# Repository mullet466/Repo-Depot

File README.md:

# Repo-Depot
Aaron's Repo Depot

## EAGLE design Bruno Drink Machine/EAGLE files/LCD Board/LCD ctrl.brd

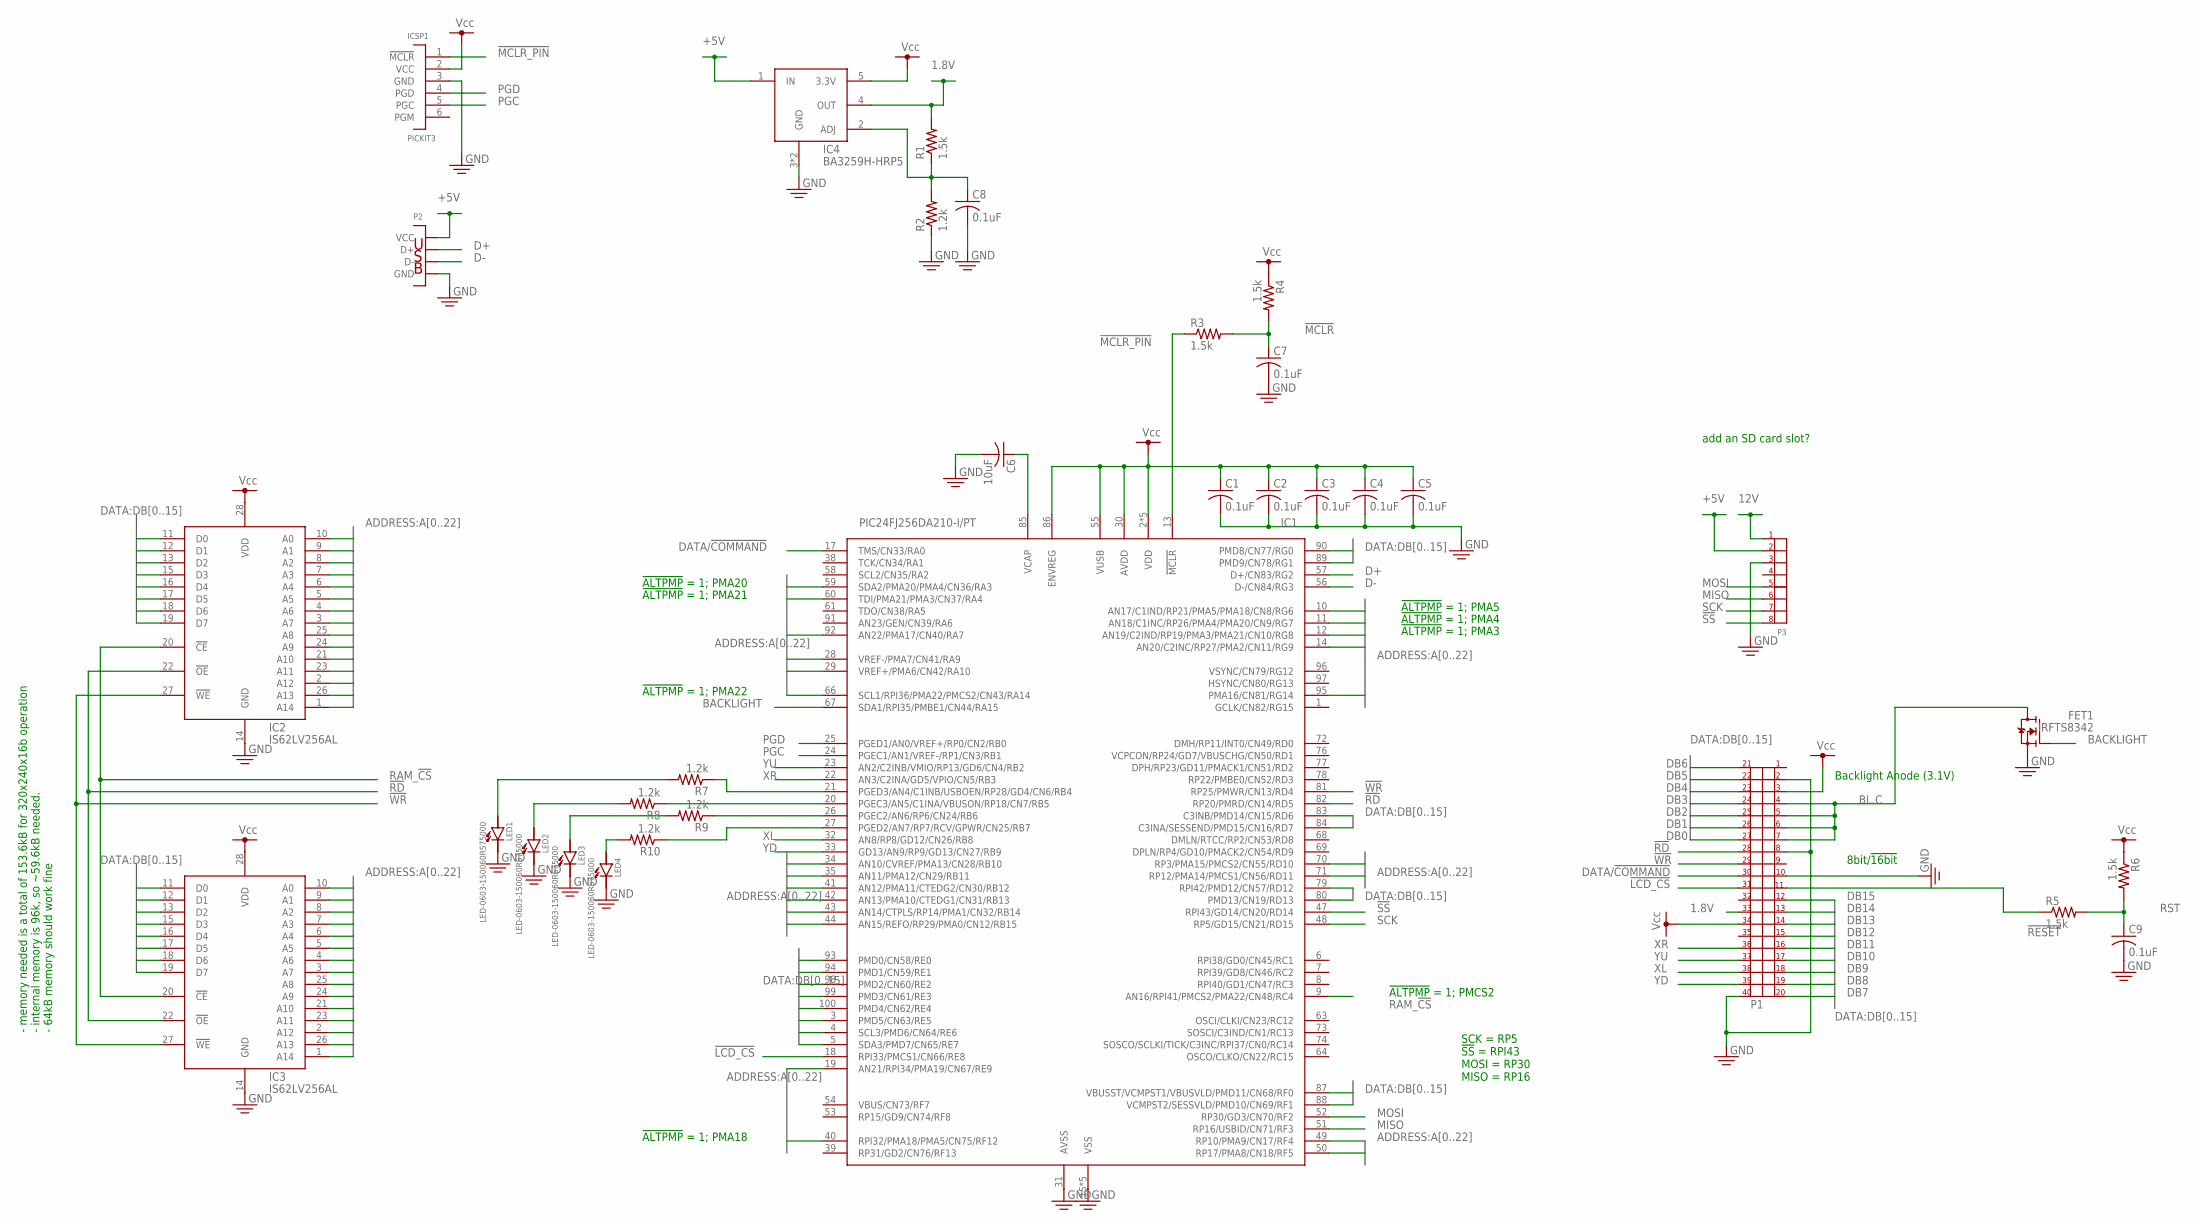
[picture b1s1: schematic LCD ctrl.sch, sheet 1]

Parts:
C1, C2, C3, C4, C5, C7, C8, C9: 0.1uF; C0603
C6: 10uF; C1206
FET1: IRFTS8342; SOT23-6
IC1: PIC24FJ256DA210-I/PT; 100-TQFP(0.4MM)
IC2, IC3: IS62LV256AL; 28-SOIC
IC4: BA3259H-HRP5; HRP5
ICSP1: PICKIT3
LED1, LED2, LED3, LED4: LED-0603-150060RS75000; 0603-LED
P1: CONN-40P-62684-401100ALF; 62684-401100ALF
P2: USB-CON690-005-299-043; USB-CON(690-005-299-043)
P3: CONN-8P-PND; B08B-PND
R1, R3, R4, R5, R6: 1.5k; R0603
R2, R7, R8, R9, R10: 1.2k; R0603

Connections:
1.8V: IC4.4 (OUT), P1.33, R1.2
12V: P3.1
!LCD_CS: IC1.18 (RPI33/PMCS1/CN66/RE8), P1.31
!MCLR: C7.1, R3.2, R4.2
!MCLR_PIN: IC1.13 (!MCLR), ICSP1.1 (!MCLR), R3.1
!RD: IC1.82 (RP20/PMRD/CN14/RD5), IC2.22 (!OE), IC3.22 (!OE), P1.28
!RESET: P1.11, R5.1
!SS: IC1.47 (RPI43/GD14/CN20/RD14), P3.8
!WR: IC1.81 (RP25/PMWR/CN13/RD4), IC2.27 (!WE), IC3.27 (!WE), P1.29
+5V: IC4.1 (IN), P2.1 (VCC), P3.2
A0: IC1.44 (AN15/REFO/RP29/PMA0/CN12/RB15), IC2.10 (A0), IC3.10 (A0)
A1: IC1.43 (AN14/CTPLS/RP14/PMA1/CN32/RB14), IC2.9 (A1), IC3.9 (A1)
A2: IC1.14 (AN20/C2INC/RP27/PMA2/CN11/RG9), IC2.8 (A2), IC3.8 (A2)
A3: IC1.12 (AN19/C2IND/RP19/PMA3/PMA21/CN10/RG8), IC2.7 (A3), IC3.7 (A3)
A4: IC1.11 (AN18/C1INC/RP26/PMA4/PMA20/CN9/RG7), IC2.6 (A4), IC3.6 (A4)
A5: IC1.10 (AN17/C1IND/RP21/PMA5/PMA18/CN8/RG6), IC2.5 (A5), IC3.5 (A5)
A6: IC1.29 (VREF+/PMA6/CN42/RA10), IC2.4 (A6), IC3.4 (A6)
A7: IC1.28 (VREF-/PMA7/CN41/RA9), IC2.3 (A7), IC3.3 (A7)
A8: IC1.50 (RP17/PMA8/CN18/RF5), IC2.25 (A8), IC3.25 (A8)
A9: IC1.49 (RP10/PMA9/CN17/RF4), IC2.24 (A9), IC3.24 (A9)
A10: IC1.42 (AN13/PMA10/CTEDG1/CN31/RB13), IC2.21 (A10), IC3.21 (A10)
A11: IC1.41 (AN12/PMA11/CTEDG2/CN30/RB12), IC2.23 (A11), IC3.23 (A11)
A12: IC1.35 (AN11/PMA12/CN29/RB11), IC2.2 (A12), IC3.2 (A12)
A13: IC1.34 (AN10/CVREF/PMA13/CN28/RB10), IC2.26 (A13), IC3.26 (A13)
A14: IC1.71 (RP12/PMA14/PMCS1/CN56/RD11), IC2.1 (A14), IC3.1 (A14)
A15: IC1.70 (RP3/PMA15/PMCS2/CN55/RD10)
A16: IC1.95 (PMA16/CN81/RG14)
A17: IC1.92 (AN22/PMA17/CN40/RA7)
A18: IC1.40 (RPI32/PMA18/PMA5/CN75/RF12)
A19: IC1.19 (AN21/RPI34/PMA19/CN67/RE9)
A20: IC1.59 (SDA2/PMA20/PMA4/CN36/RA3)
A21: IC1.60 (TDI/PMA21/PMA3/CN37/RA4)
A22: IC1.66 (SCL1/RPI36/PMA22/PMCS2/CN43/RA14)
BACKLIGHT: FET1.3 (G), IC1.67 (SDA1/RPI35/PMBE1/CN44/RA15)
BL.C: FET1.1 (D), FET1.2 (D), FET1.5 (D), FET1.6 (D), P1.4, P1.5, P1.6, P1.7
D+: IC1.57 (D+/CN83/RG2), P2.3 (D+)
D-: IC1.56 (D-/CN84/RG3), P2.2 (D-)
DATA/!COMMAND: IC1.17 (TMS/CN33/RA0), P1.30
DB0: IC1.93 (PMD0/CN58/RE0), IC3.11 (D0), P1.27
DB1: IC1.94 (PMD1/CN59/RE1), IC3.12 (D1), P1.26
DB2: IC1.98 (PMD2/CN60/RE2), IC3.13 (D2), P1.25
DB3: IC1.99 (PMD3/CN61/RE3), IC3.15 (D3), P1.24
DB4: IC1.100 (PMD4/CN62/RE4), IC3.16 (D4), P1.23
DB5: IC1.3 (PMD5/CN63/RE5), IC3.17 (D5), P1.22
DB6: IC1.4 (SCL3/PMD6/CN64/RE6), IC3.18 (D6), P1.21
DB7: IC1.5 (SDA3/PMD7/CN65/RE7), IC3.19 (D7), P1.20
DB8: IC1.90 (PMD8/CN77/RG0), IC2.11 (D0), P1.19
DB9: IC1.89 (PMD9/CN78/RG1), IC2.12 (D1), P1.18
DB10: IC1.88 (VCMPST2/SESSVLD/PMD10/CN69/RF1), IC2.13 (D2), P1.17
DB11: IC1.87 (VBUSST/VCMPST1/VBUSVLD/PMD11/CN68/RF0), IC2.15 (D3), P1.16
DB12: IC1.79 (RPI42/PMD12/CN57/RD12), IC2.16 (D4), P1.15
DB13: IC1.80 (PMD13/CN19/RD13), IC2.17 (D5), P1.14
DB14: IC1.83 (C3INB/PMD14/CN15/RD6), IC2.18 (D6), P1.13
DB15: IC1.84 (C3INA/SESSEND/PMD15/CN16/RD7), IC2.19 (D7), P1.12
GND: C1.2, C2.2, C3.2, C4.2, C5.2, C6.2, C7.2, C8.2, C9.2, FET1.4 (S), IC1.15 (VSS), IC1.31 (AVSS), IC1.36 (VSS), IC1.45 (VSS), IC1.65 (VSS), IC1.75 (VSS), IC2.14 (GND), IC3.14 (GND), IC4.3 (GND), IC4.FIN (GND), ICSP1.3 (GND), LED1.C, LED2.C, LED3.C, LED4.C, P1.2, P1.8, P1.10, P1.40, P2.5 (GND), P2./GND (GND), P2./GND1 (GND), P2.GND, P2.GND1 (GND), P3.3, R2.1
MISO: IC1.51 (RP16/USBID/CN71/RF3), P3.6
MOSI: IC1.52 (RP30/GD3/CN70/RF2), P3.5
unnamed: C8.1, IC4.2 (ADJ), R1.1, R2.2
unnamed: IC1.21 (PGED3/AN4/C1INB/USBOEN/RP28/GD4/CN6/RB4), R7.1
unnamed: IC1.20 (PGEC3/AN5/C1INA/VBUSON/RP18/CN7/RB5), R8.1
unnamed: C6.1, IC1.85 (VCAP)
unnamed: IC1.26 (PGEC2/AN6/RP6/CN24/RB6), R9.1
unnamed: IC1.27 (PGED2/AN7/RP7/RCV/GPWR/CN25/RB7), R10.1
unnamed: LED4.A, R10.2
unnamed: LED3.A, R9.2
unnamed: LED2.A, R8.2
unnamed: LED1.A, R7.2
PGC: IC1.24 (PGEC1/AN1/VREF-/RP1/CN3/RB1), ICSP1.5 (PGC)
PGD: IC1.25 (PGED1/AN0/VREF+/RP0/CN2/RB0), ICSP1.4 (PGD)
RAM_!CS: IC1.9 (AN16/RPI41/PMCS2/PMA22/CN48/RC4), IC2.20 (!CE), IC3.20 (!CE)
RST: C9.1, R5.2, R6.2
SCK: IC1.48 (RP5/GD15/CN21/RD15), P3.7
VCC: C1.1, C2.1, C3.1, C4.1, C5.1, IC1.2 (VDD), IC1.16 (VDD), IC1.30 (AVDD), IC1.37 (VDD), IC1.46 (VDD), IC1.55 (VUSB), IC1.62 (VDD), IC1.86 (ENVREG), IC2.28 (VDD), IC3.28 (VDD), IC4.5 (3.3V), ICSP1.2 (VCC), P1.3, P1.34, R4.1, R6.1
XL: IC1.32 (AN8/RP8/GD12/CN26/RB8), P1.38
XR: IC1.22 (AN3/C2INA/GD5/VPIO/CN5/RB3), P1.36
YD: IC1.33 (GD13/AN9/RP9/GD13/CN27/RB9), P1.39
YU: IC1.23 (AN2/C2INB/VMIO/RP13/GD6/CN4/RB2), P1.37

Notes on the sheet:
- memory needed is a total of 153.6kB for 320x240x16b operation - internal memory is 96k, so ~59.6kB needed. - 64kB memory should work fine
!ALTPMP! = 1; PMA22
!ALTPMP! = 1; PMCS2
!ALTPMP! = 1; PMA18
!ALTPMP! = 1; PMA5
!ALTPMP! = 1; PMA4
!ALTPMP! = 1; PMA3
!ALTPMP! = 1; PMA20
!ALTPMP! = 1; PMA21
Backlight Anode (3.1V)
8bit/!16bit!
SCK = RP5 !SS! = RPI43 MOSI = RP30 MISO = RP16
add an SD card slot?

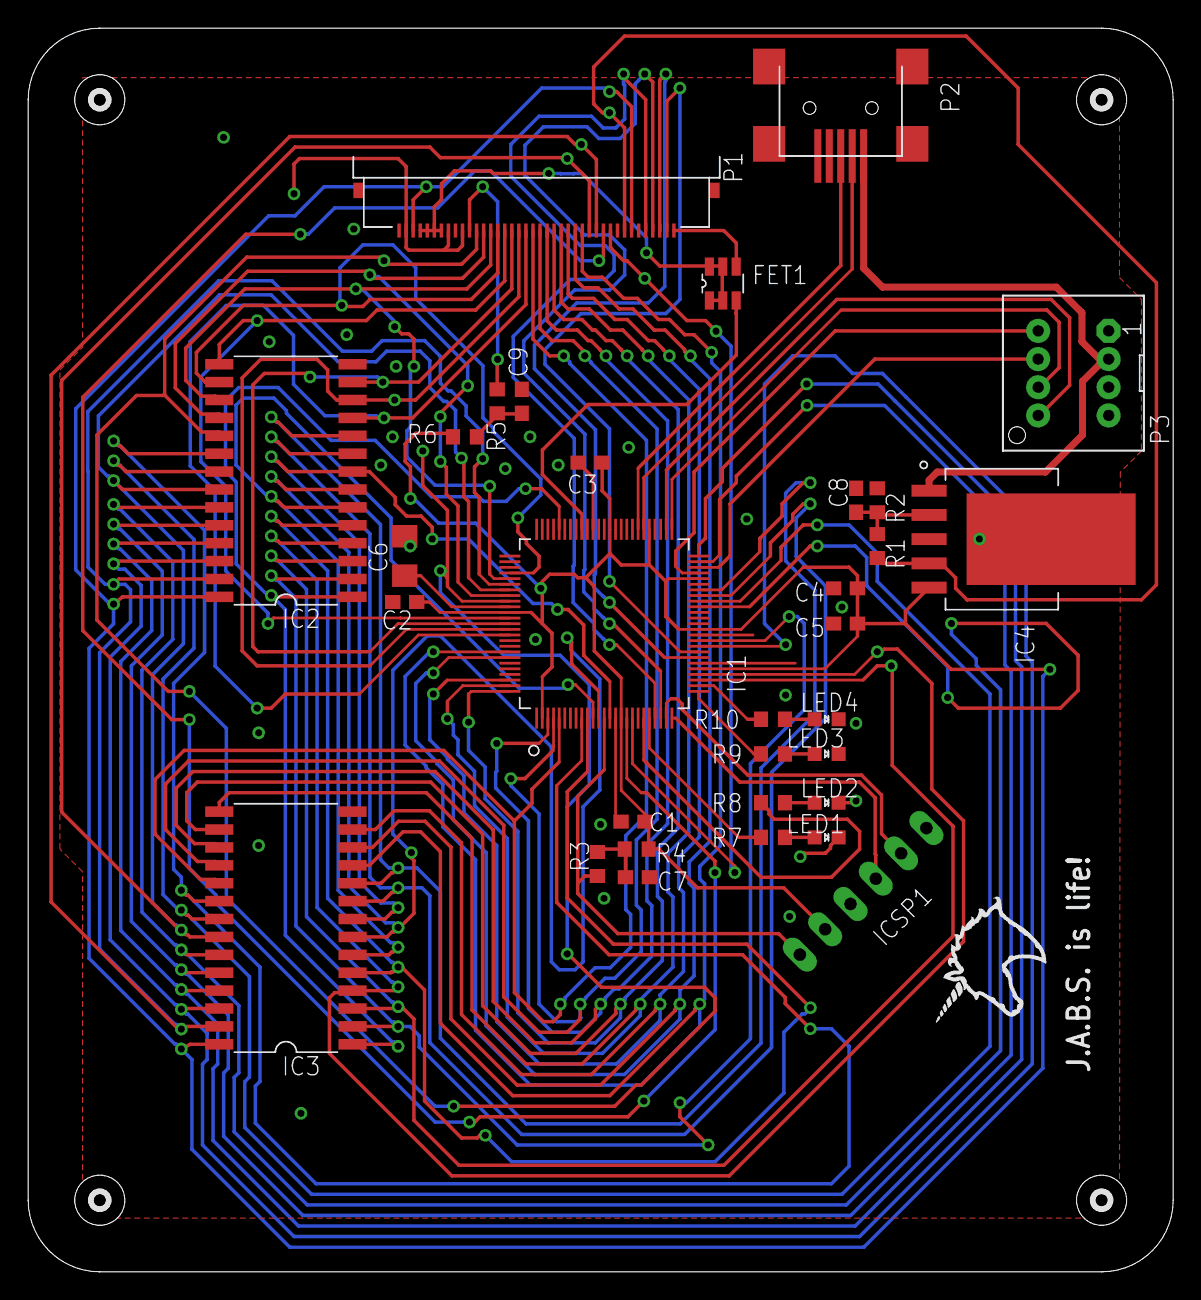
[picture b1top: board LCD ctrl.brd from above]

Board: 2 copper layers, 80.8 x 87.8 mm, 38 parts (0 on the bottom side), 68 nets.

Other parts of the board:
U$20: UNICORN-SCREEN
U$32, U$33, U$34, U$35: #6-32
U$36: JABS

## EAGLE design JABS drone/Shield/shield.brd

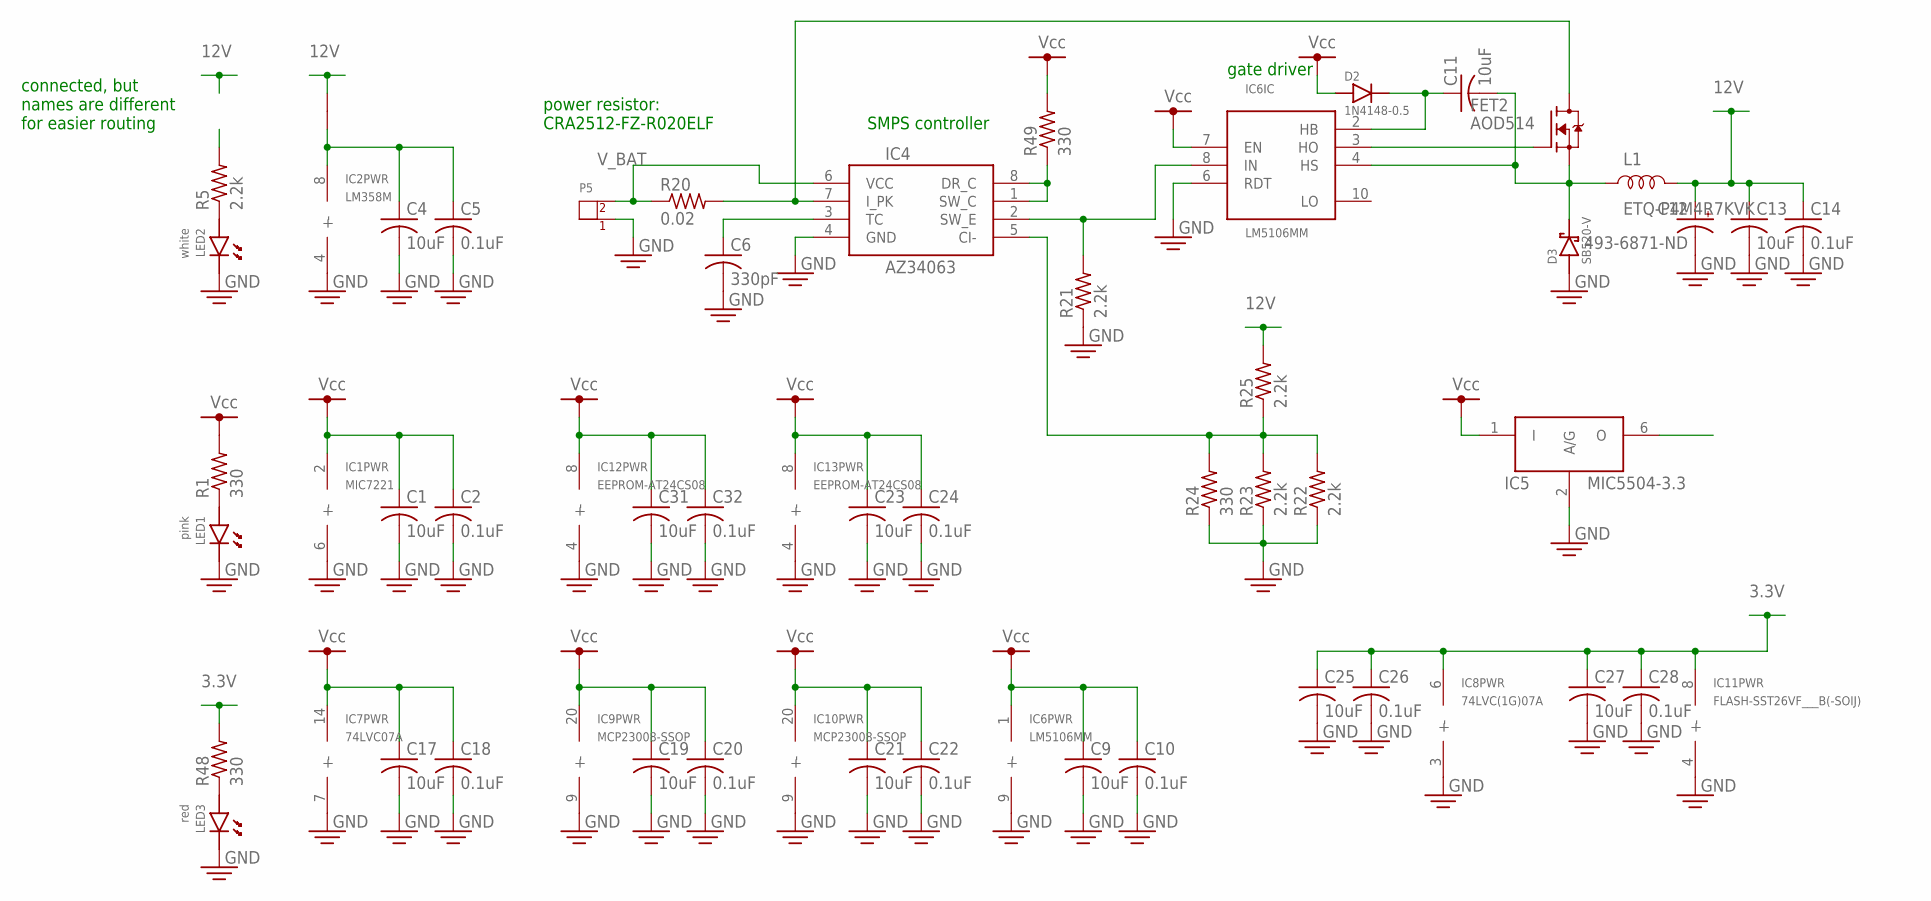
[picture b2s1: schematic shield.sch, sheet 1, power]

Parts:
-1: SEPERATOR
C1, C4, C9, C11, C13, C17, C19, C21, C23, C25, C27, C31: 10uF; C0805
C2, C5, C10, C14, C18, C20, C22, C24, C26, C28, C32: 0.1uF; C0603
C6: 330pF; C0603
C12: 493-6871-ND; E5-13
D2: 1N4148-0.5; DIODE-5
D3: SB520-V
FET2: AOD514; TO-252
IC1: MIC7221; SOT23-5
IC2: LM358M; 8-SOP
IC4: AZ34063; 8-SOP
IC5: MIC5504-3.3; SOT23-5
IC6: LM5106MM; 10-VSSOP
IC7: 74LVC07A; 14-SOP
IC8: 74LVC(1G)07A; SOT23-5
IC9, IC10: MCP23008-SSOP; 20-SSOP(0.65MM)
IC11: FLASH-SST26VF___B(-SOIJ); 8-SOIJ
IC12, IC13: EEPROM-AT24CS08; 8-SOP
L1: ETQ-P4M4R7KVK; INDUCTOR-ETQ__K
LED1: pink; LED5MM
LED2: white; LED5MM
LED3: red; LED5MM
P5: CONN-2P-VL; B02P-VL
R1, R24, R48, R49: 330; R0603
R5, R21, R22, R23, R25: 2.2k; R0603
R20: 0.02; R2512

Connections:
3.3V: C25.1, C26.1, C27.1, C28.1, IC8.6 (+), IC11.8 (+), R48.2; also elsewhere on the board
12V: -1.P$2, C12.+, C13.1, C14.1, L1.2 (B), R25.2; also elsewhere on the board
GND: C1.2, C2.2, C4.2, C5.2, C6.2, C9.2, C10.2, C12.-, C13.2, C14.2, C17.2, C18.2, C19.2, C20.2, C21.2, C22.2, C23.2, C24.2, C25.2, C26.2, C27.2, C28.2, C31.2, C32.2, D3.A, IC1.6 (-), IC2.4 (-), IC4.4 (GND), IC5.2 (A/G), IC6.6 (RDT), IC6.9 (-), IC7.7 (-), IC8.3 (-), IC9.9 (-), IC10.9 (-), IC11.4 (-), IC12.4 (-), IC13.4 (-), LED1.C, LED2.C, LED3.C, P5.1, R21.1, R22.1, R23.1, R24.1; also elsewhere on the board
IO_3.3V: IC5.6 (O); also elsewhere on the board
unnamed: LED1.A, R1.1
unnamed: LED2.A, R5.1
unnamed: C6.1, IC4.3 (TC)
unnamed: FET2.TAB (D), IC4.7 (I_PK), R20.2
unnamed: C11.1, D2.C, IC6.2 (HB)
unnamed: C11.2, D3.K (C), FET2.2 (S), IC6.4 (HS), L1.1 (A)
unnamed: FET2.1 (G), IC6.3 (HO)
unnamed: IC4.2 (SW_E), IC6.8 (IN), R21.2
unnamed: IC4.5 (CI-), R22.2, R23.2, R24.2, R25.1
unnamed: LED3.A, R48.1
unnamed: IC4.1 (SW_C), IC4.8 (DR_C), R49.1
unnamed: -1.P$1, C4.1, C5.1, IC2.8 (+)
VCC: C1.1, C2.1, C9.1, C10.1, C17.1, C18.1, C19.1, C20.1, C21.1, C22.1, C23.1, C24.1, C31.1, C32.1, D2.A, IC1.2 (+), IC5.1 (I), IC6.1 (+), IC6.7 (EN), IC7.14 (+), IC9.20 (+), IC10.20 (+), IC12.8 (+), IC13.8 (+), R1.2, R49.2; also elsewhere on the board
VIN: R5.2; also elsewhere on the board
V_BAT: IC4.6 (VCC), P5.2, R20.1; also elsewhere on the board

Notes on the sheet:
SMPS controller
gate driver
power resistor: CRA2512-FZ-R020ELF
connected, but names are different for easier routing

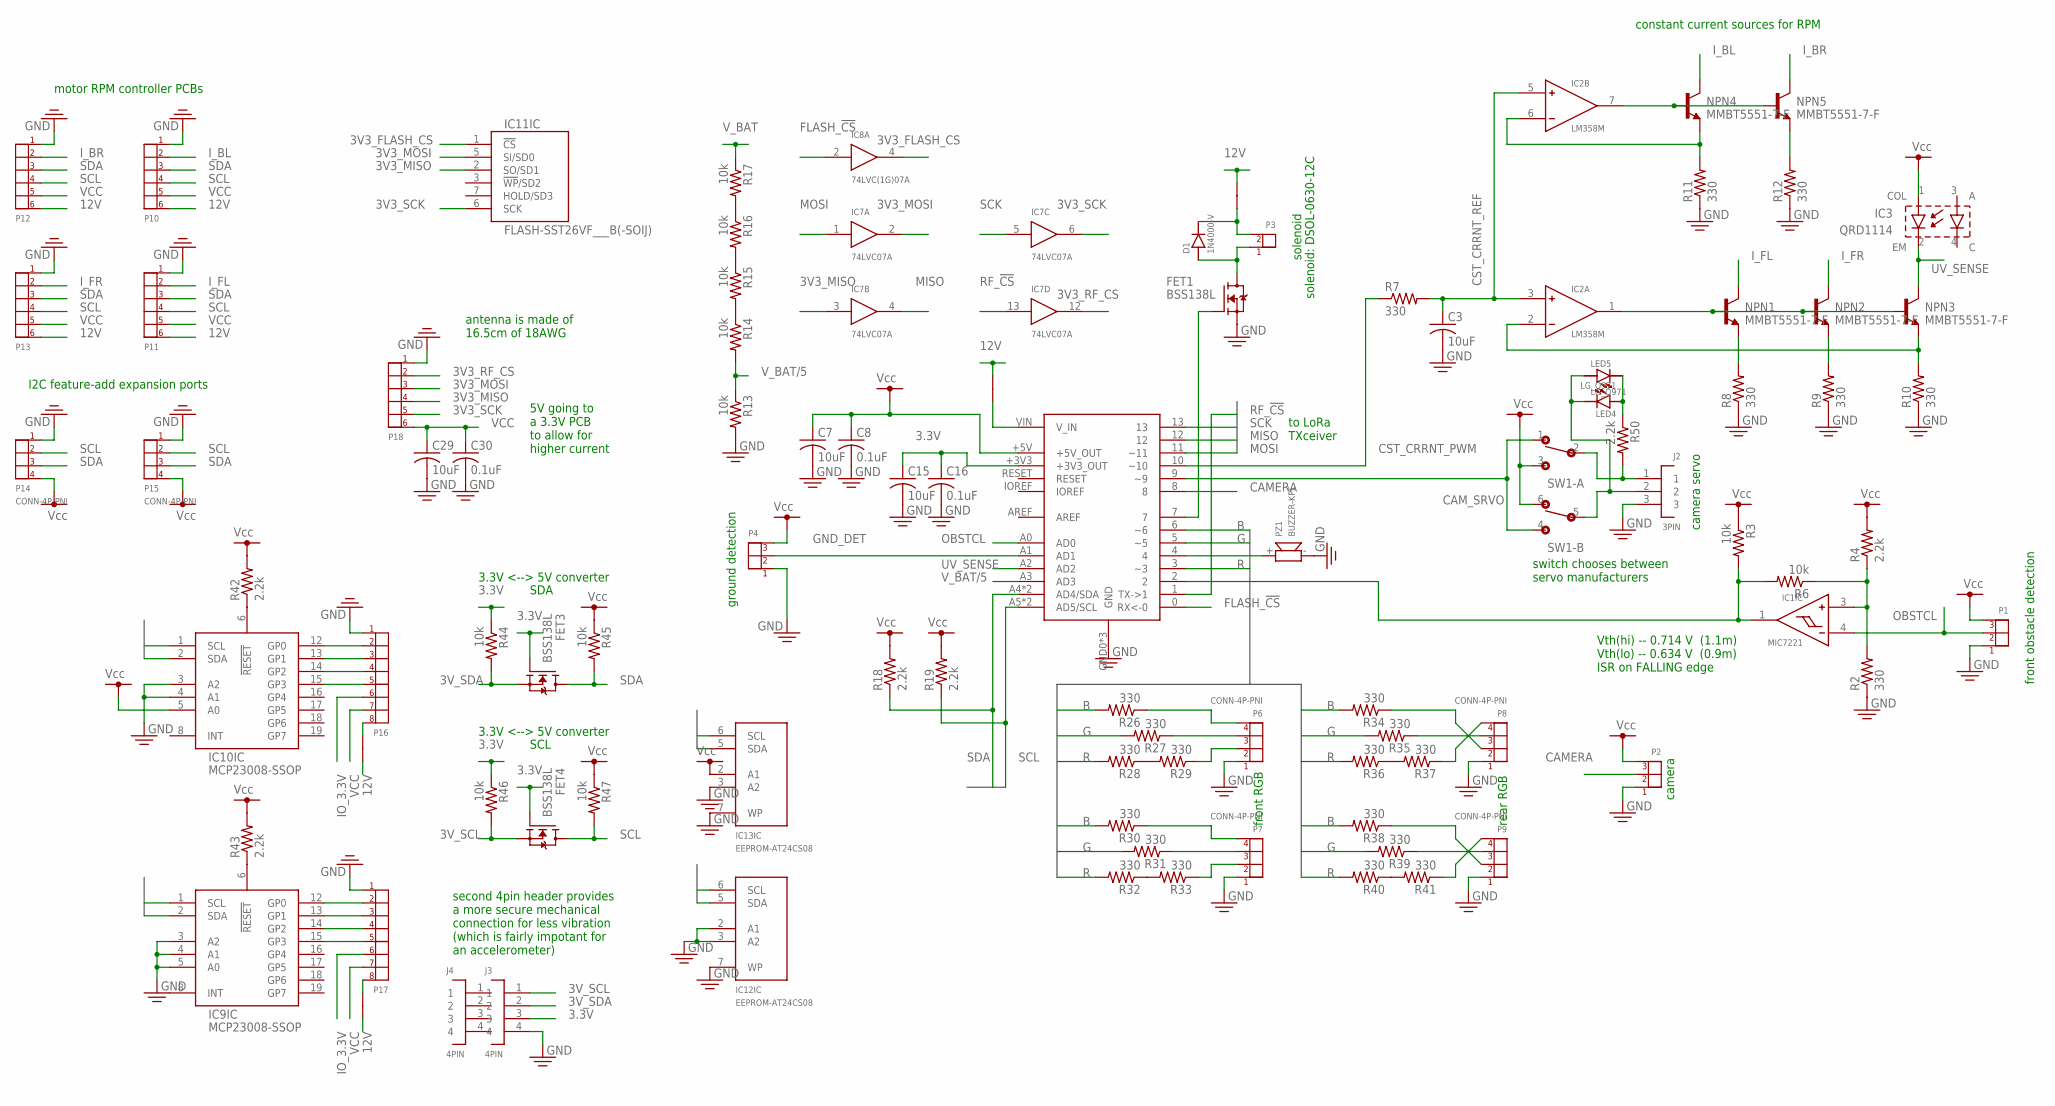
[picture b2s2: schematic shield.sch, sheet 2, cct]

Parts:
-2, -3, -4, -5: SEPERATOR
C3, C7, C15, C29: 10uF; C0805
C8, C16, C30: 0.1uF; C0603
D1: 1N4000-V; DIODE-V
FET1, FET3, FET4: BSS138L; SOT-23
IC1: MIC7221; SOT23-5
IC2: LM358M; 8-SOP
IC3: QRD1114
IC7: 74LVC07A; 14-SOP
IC8: 74LVC(1G)07A; SOT23-5
IC9, IC10: MCP23008-SSOP; 20-SSOP(0.65MM)
IC11: FLASH-SST26VF___B(-SOIJ); 8-SOIJ
IC12, IC13: EEPROM-AT24CS08; 8-SOP
J1: ARDUINO_UNO
J2: 3PIN; 3P
J3, J4: 4PIN; 4P
LED4, LED5: LG_Q971; 0603-LED
NPN1, NPN2, NPN3, NPN4, NPN5: MMBT5551-7-F; SOT-23
P1, P2, P4: CONN-3P-PNI; B03B-PNISK
P3: CONN-2P-PNI; B02B-PNISK
P6, P7, P8, P9, P14, P15: CONN-4P-PNI; B04B-PNISK
P10, P11, P12, P13, P18: CONN-6P-PNI; B06B-PNISK
P16, P17: CONN-8P-PNI; B08B-PNISK
PZ1: BUZZER-KPE; KPE-242
R2, R7, R8, R9, R10, R11, R12, R26, R27, R28, R29, R30, R31, R32, R33, R34, R35, R36, R37, R38, R39, R40, R41: 330; R0603
R3, R6, R13, R14, R15, R16, R17, R44, R45, R46, R47: 10k; R0603
R4, R18, R19, R42, R43, R50: 2.2k; R0603
SW1: SWITCH-DPDT-JS202011SCQN; JS202011SCQN

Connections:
3.3V: C15.1, C16.1, FET3.1 (G), FET4.1 (G), J1.+3V3 (+3V3_OUT), J3.3, R44.1, R46.1; also elsewhere on the board
3V3_FLASH_CS: IC8.4 (OUT), IC11.1 (!CS!)
3V3_MISO: IC7.3 (IN), IC11.2 (SO/SD1), P18.4
3V3_MOSI: IC7.2 (OUT), IC11.5 (SI/SD0), P18.3
3V3_RF_CS: IC7.12 (OUT), P18.2
3V3_SCK: IC7.6 (OUT), IC11.6 (SCK), P18.5
3V_SCL: FET4.2 (S), J3.1, R46.2
3V_SDA: FET3.2 (S), J3.2, R44.2
12V: -2.P$2, -3.P$2, -4.P$1, -5.P$1, P10.6, P11.6, P12.6, P13.6; also elsewhere on the board
B: J1.6 (~6), R26.2, R30.2, R34.2, R38.2
CAMERA: J1.8, P2.2
CAM_SRVO: J1.9 (~9), SW1.1 (NC), SW1.4 (NO)
CST_CRRNT_PWM: J1.10 (~10), R7.1
CST_CRRNT_REF: C3.1, IC2.3 (+), IC2.5 (+), R7.2
FLASH_!CS!: IC8.2 (IN), J1.0 (RX<-0)
G: J1.5 (~5), R27.2, R31.2, R35.2, R39.2
GND: C3.2, C7.2, C8.2, C15.2, C16.2, C29.2, C30.2, FET1.2 (S), IC9.3 (A2), IC9.4 (A1), IC9.5 (A0), IC10.3 (A2), IC10.4 (A1), IC12.2 (A1), IC12.3 (A2), IC12.7 (WP), IC13.3 (A2), IC13.7 (WP), J1.GND0 (GND), J1.GND1 (GND), J1.GND2 (GND), J2.3, J3.4, P1.1, P2.1, P4.1, P6.1, P7.1, P8.1, P9.1, P10.1, P11.1, P12.1, P13.1, P14.1, P15.1, P16.1, P17.1, P18.1, PZ1.-, R2.1, R8.1, R9.1, R10.1, R11.1, R12.1, R13.2; also elsewhere on the board
GND_DET: J1.A1 (AD1), P4.2
IO_3.3V: P16.6, P17.6; also elsewhere on the board
I_BL: NPN4.3 (C), P10.2
I_BR: NPN5.3 (C), P12.2
I_FL: NPN1.3 (C), P11.2
I_FR: NPN2.3 (C), P13.2
MISO: IC7.4 (OUT), J1.12
MOSI: IC7.1 (IN), J1.11 (~11)
unnamed: R28.1, R29.2
unnamed: P6.2, R29.1
unnamed: J2.1, R50.2, SW1.2 (COM)
unnamed: IC1.3 (+), R2.2, R4.1, R6.1
unnamed: IC1.1 (OUT), J1.2, R3.2, R6.2
unnamed: J2.2, LED4.C, LED5.A, SW1.5 (COM)
unnamed: IC2.1 (OUT), NPN1.1 (B), NPN2.1 (B), NPN3.1 (B)
unnamed: IC2.7 (OUT), NPN4.1 (B), NPN5.1 (B)
unnamed: IC2.2 (-), NPN3.2 (E), R10.2
unnamed: NPN2.2 (E), R9.2
unnamed: R14.1, R15.2
unnamed: IC2.6 (-), NPN4.2 (E), R11.2
unnamed: NPN5.2 (E), R12.2
unnamed: J1.4, PZ1.+
unnamed: FET1.1 (G), J1.7
unnamed: D1.A, FET1.3 (D), P3.1
unnamed: NPN1.2 (E), R8.2
unnamed: R15.1, R16.2
unnamed: R16.1, R17.2
unnamed: P6.3, R27.1
unnamed: P6.4, R26.1
unnamed: R32.1, R33.2
unnamed: P7.2, R33.1
unnamed: P7.3, R31.1
unnamed: P7.4, R30.1
unnamed: R36.1, R37.2
unnamed: P8.4, R37.1
unnamed: P8.3, R35.1
unnamed: P8.2, R34.1
unnamed: R40.1, R41.2
unnamed: P9.4, R41.1
unnamed: P9.3, R39.1
unnamed: P9.2, R38.1
unnamed: IC9.12 (GP0), P17.2
unnamed: -3.P$1, D1.C, P3.2
unnamed: IC10.6 (!RESET!), R42.1
unnamed: IC9.6 (!RESET!), R43.1
unnamed: IC9.13 (GP1), P17.3
unnamed: IC9.14 (GP2), P17.4
unnamed: IC9.15 (GP3), P17.5
unnamed: IC10.12 (GP0), P16.2
unnamed: IC10.13 (GP1), P16.3
unnamed: IC10.14 (GP2), P16.4
unnamed: IC10.15 (GP3), P16.5
unnamed: LED4.A, LED5.C, R50.1
unnamed: -5.P$2, P16.8
unnamed: -4.P$2, P17.8
OBSTCL: IC1.4 (-), J1.A0 (AD0), P1.2
R: J1.3 (~3), R28.2, R32.2, R36.2, R40.2
RF_!CS!: IC7.13 (IN), J1.1 (TX->1)
SCK: IC7.5 (IN), J1.13
SCL: FET4.3 (D), IC9.1 (SCL), IC10.1 (SCL), IC12.6 (SCL), IC13.6 (SCL), J1.A5 (AD5/SCL), J1.SCL (AD5/SCL), P10.4, P11.4, P12.4, P13.4, P14.2, P15.2, R19.1, R47.2
SDA: FET3.3 (D), IC9.2 (SDA), IC10.2 (SDA), IC12.5 (SDA), IC13.5 (SDA), J1.A4 (AD4/SDA), J1.SDA (AD4/SDA), P10.3, P11.3, P12.3, P13.3, P14.3, P15.3, R18.1, R45.2
UV_SENSE: IC3.2 (EM), J1.A2 (AD2), NPN3.3 (C)
VCC: C7.1, C8.1, C29.1, C30.1, IC3.1 (COL), IC10.5 (A0), IC13.2 (A1), J1.+5V (+5V_OUT), P1.3, P2.3, P4.3, P10.5, P11.5, P12.5, P13.5, P14.4, P15.4, P16.7, P17.7, P18.6, R3.1, R4.2, R18.2, R19.2, R42.2, R43.2, R45.1, R47.1, SW1.3 (NO), SW1.6 (NC); also elsewhere on the board
VIN: -2.P$1, J1.VIN (V_IN); also elsewhere on the board
V_BAT: R17.1; also elsewhere on the board
V_BAT/5: J1.A3 (AD3), R13.1, R14.2

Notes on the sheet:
front obstacle detection
Vth(hi) -- 0.714 V (1.1m) Vth(lo) -- 0.634 V (0.9m) ISR on FALLING edge
camera
camera servo
switch chooses between servo manufacturers
solenoid
constant current sources for RPM
ground detection
solenoid: DSOL-0630-12C
to LoRa TXceiver
front RGB
rear RGB
antenna is made of 16.5cm of 18AWG
second 4pin header provides a more secure mechanical connection for less vibration (which is fairly impotant for an accelerometer)
SDA
SCL
3.3V <--> 5V converter
motor RPM controller PCBs
I2C feature-add expansion ports
5V going to a 3.3V PCB to allow for higher current

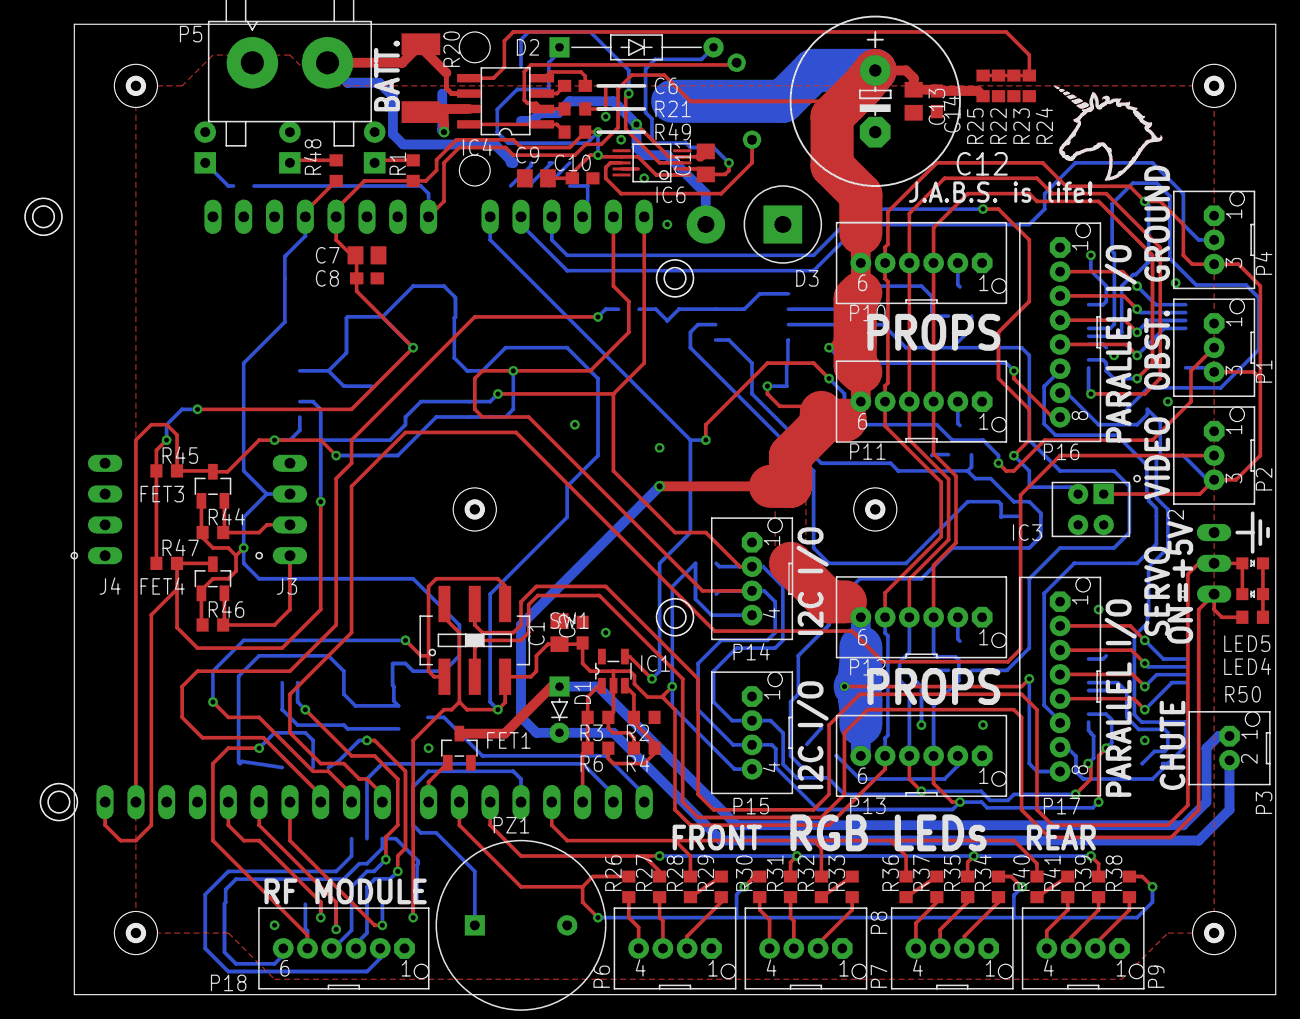
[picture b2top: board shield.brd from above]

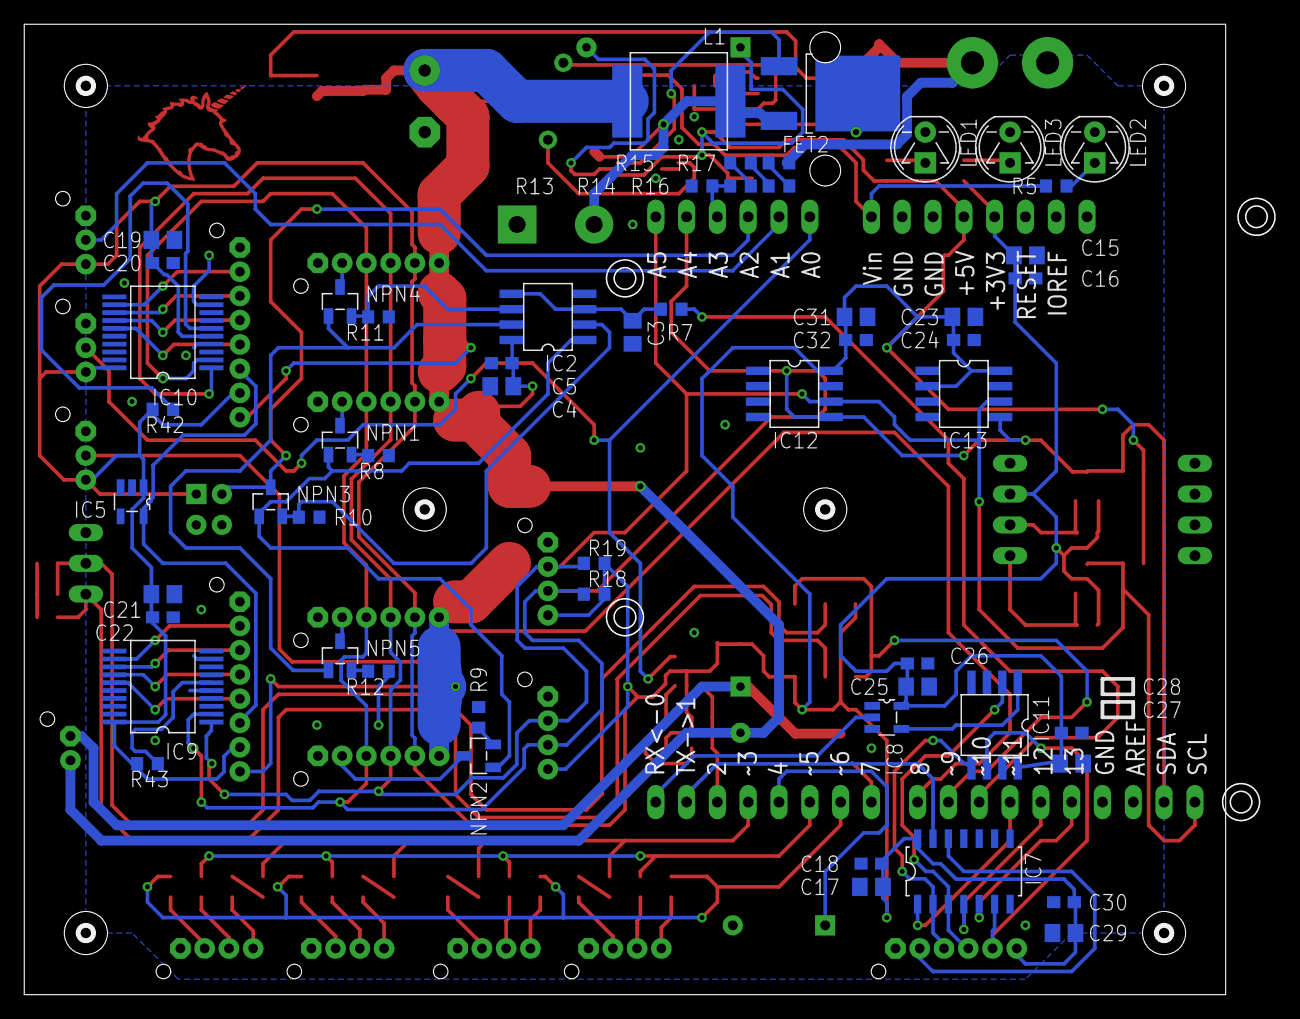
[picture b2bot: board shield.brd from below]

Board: 2 copper layers, 102.8 x 79.6 mm, 153 parts (58 on the bottom side), 95 nets.

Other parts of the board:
U$58: UNICORN-SCREEN
U$78: UNICORN-TOP
U$88, U$112, U$114, U$115, U$116, U$117: #6-32
U$124, U$125: FIDUCIAL_MARKER
U$126: JABS

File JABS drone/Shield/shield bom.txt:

"Qty";"Value";"Device";"Package";"Parts";"Description";"";
"1";"0.02";"R-US_R2512";"R2512";"R20";"RESISTOR, American symbol";"";
"14";"0.1uF";"C-USC0603";"C0603";"C2, C5, C8, C10, C14, C16, C18, C20, C22, C24, C26, C28, C30, C32";"CAPACITOR, American symbol";"";
"11";"10k";"R-US_R0603";"R0603";"R3, R6, R13, R14, R15, R16, R17, R44, R45, R46, R47";"RESISTOR, American symbol";"";
"16";"10uF";"C-USC0805";"C0805";"C1, C3, C4, C7, C9, C11, C13, C15, C17, C19, C21, C23, C25, C27, C29, C31";"CAPACITOR, American symbol";"";
"1";"1N4000-V";"1N4000-V";"DIODE-V";"D1";"";"";
"1";"1N4148-0.5";"1N4148-0.5";"DIODE-5";"D2";"";"";
"11";"2.2k";"R-US_R0603";"R0603";"R4, R5, R18, R19, R21, R22, R23, R25, R42, R43, R50";"RESISTOR, American symbol";"";
"27";"330";"R-US_R0603";"R0603";"R1, R2, R7, R8, R9, R10, R11, R12, R24, R26, R27, R28, R29, R30, R31, R32, R33, R34, R35, R36, R37, R38, R39, R40, R41, R48, R49";"RESISTOR, American symbol";"";
"1";"330pF";"C-USC0603";"C0603";"C6";"CAPACITOR, American symbol";"";
"1";"3PIN";"3PIN";"3P";"J2";"";"";
"1";"493-6871-ND";"CPOL-USE5-13";"E5-13";"C12";"POLARIZED CAPACITOR, American symbol";"";
"2";"4PIN";"4PIN";"4P";"J3, J4";"";"";
"1";"74LVC(1G)07A";"74LVC(1G)07A";"SOT23-5";"IC8";"";"";
"1";"74LVC07A";"74LVC07A";"14-SOP";"IC7";"hex buffer with open collector outputs";"";
"1";"AOD514";"AOD514";"TO-252";"FET2";"";"";
"1";"ARDUINO_UNO";"ARDUINO_UNO";"ARDUINO_UNO";"J1";"footprint for the header pins on most simple Arduino boards, such as the Uno and Duemilanove";"";
"1";"AZ34063";"AZ34063";"8-SOP";"IC4";"";"";
"3";"BSS138L";"BSS138L";"SOT-23";"FET1, FET3, FET4";"N.ch enhancement mode MOSFET";"";
"1";"BUZZER-KPE";"BUZZER-KPE";"KPE-242";"PZ1";"";"";
"1";"CONN-2P-PNI";"CONN-2P-PNI";"B02B-PNISK";"P3";"";"";
"1";"CONN-2P-VL";"CONN-2P-VL";"B02P-VL";"P5";"";"";
"3";"CONN-3P-PNI";"CONN-3P-PNI";"B03B-PNISK";"P1, P2, P4";"";"";
"6";"CONN-4P-PNI";"CONN-4P-PNI";"B04B-PNISK";"P6, P7, P8, P9, P14, P15";"";"";
"5";"CONN-6P-PNI";"CONN-6P-PNI";"B06B-PNISK";"P10, P11, P12, P13, P18";"";"";
"2";"CONN-8P-PNI";"CONN-8P-PNI";"B08B-PNISK";"P16, P17";"";"";
"2";"EEPROM-AT24CS08";"EEPROM-AT24CS08";"8-SOP";"IC12, IC13";"generic I2C EEPROM";"";
"1";"ETQ-P4M4R7KVK";"INDUCTOR-ETQ___K";"INDUCTOR-ETQ__K";"L1";"";"";
"1";"FLASH-SST26VF___B";"FLASH-SST26VF___B";"8-SOP";"IC11";"";"";
"2";"LG_Q971";"LG_Q971";"0603-LED";"LED4, LED5";"0603 LED; red, orange, yellow, or green";"";
"1";"LM358M";"LM358M";"8-SOP";"IC2";"";"";
"1";"LM5106MM";"LM5106MM";"10-VSSOP";"IC6";"";"";
"2";"MCP23008-SSOP";"MCP23008-SSOP";"20-SSOP(0.65MM)";"IC9, IC10";"";"";
"1";"MIC5504-3.3";"MIC5504-3.3";"SOT23-5";"IC5";"3.3V regulator, 5.5V max input, 300mA output";"";
"1";"MIC7221";"MIC7221";"SOT23-5";"IC1";"";"";
"5";"MMBT5551-7-F-SOT23";"MMBT5551-7-F-SOT23";"SOT-23";"NPN1, NPN2, NPN3, NPN4, NPN5";"";"";
"1";"QRD1114";"QRD1114";"QRD1114";"IC3";"";"";
"1";"SB520-V";"SB520-V";"SB520-V";"D3";"";"";
"5";"SEPERATOR";"SEPERATOR";"SEPERATOR";"-1, -2, -3, -4, -5";"seperates wide, hard-to-route power rails from thin supply traces";"";
"1";"SWITCH-DPDT-JS202011SCQN";"SWITCH-DPDT-JS202011SCQN";"JS202011SCQN";"SW1";"";"";
"1";"pink";"LED5MM";"LED5MM";"LED1";"";"";
"1";"red";"LED5MM";"LED5MM";"LED3";"";"";
"1";"white";"LED5MM";"LED5MM";"LED2";"";"";

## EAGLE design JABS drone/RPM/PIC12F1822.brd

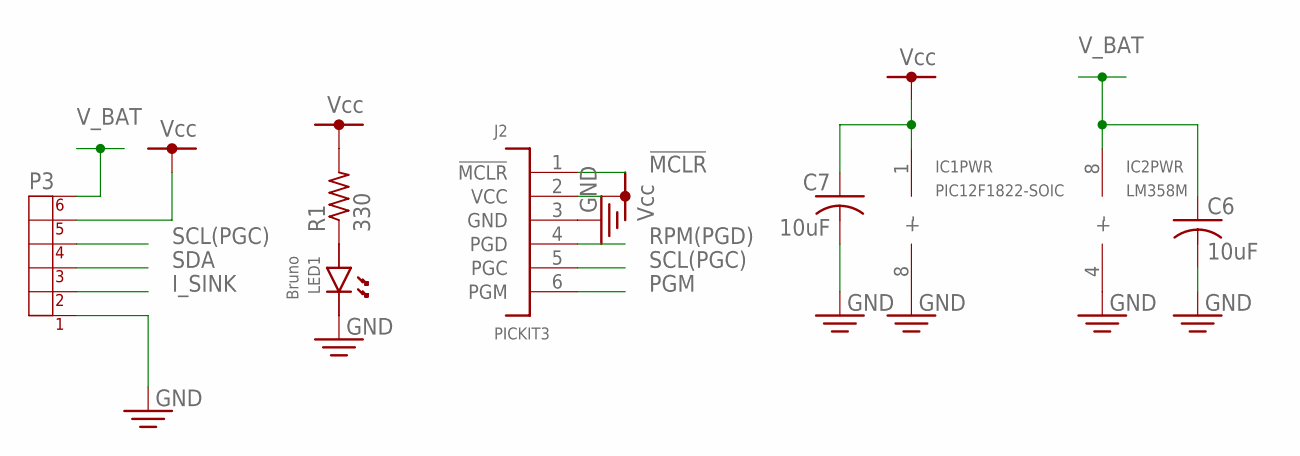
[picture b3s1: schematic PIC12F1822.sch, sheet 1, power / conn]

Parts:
C6, C7: 10uF; C0805
IC1: PIC12F1822-SOIC; 8-SOP
IC2: LM358M; 8-SOP
J2: PICKIT3
LED1: Bruno; LED3MM
P3: CONN-6P-PNI; B06B-PNISK
R1: 330; R0805

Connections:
!MCLR: J2.1 (!MCLR); also elsewhere on the board
GND: C6.2, C7.2, IC1.8 (-), IC2.4 (-), J2.3 (GND), LED1.C, P3.1; also elsewhere on the board
I_SINK: P3.2; also elsewhere on the board
unnamed: LED1.A, R1.1
PGM: J2.6 (PGM)
RPM(PGD): J2.4 (PGD); also elsewhere on the board
SCL(PGC): J2.5 (PGC), P3.4; also elsewhere on the board
SDA: P3.3; also elsewhere on the board
VCC: C7.1, IC1.1 (+), J2.2 (VCC), P3.5, R1.2; also elsewhere on the board
V_BAT: C6.1, IC2.8 (+), P3.6; also elsewhere on the board
